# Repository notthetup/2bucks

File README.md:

# 2bucks 💰
A simple PCB with 2 DCDC (buck) regulators

## Description

This PCB solves the requirement for having 2 low-power lower voltage power rails generated from a higher voltage (usually 24V) rails for testing small project. Instead of sticking multiple small DC-DC modules which makes cabling a mess, I thought it would be simpler to make a quick PCB.

The PCB is designed to be as small as possible, and I also forgot to add any mounting holes. **Oops!**

It uses screw termnials for input and output It currently targets the [MornSun SIP DC-DC modules](https://www.mornsun-power.com/html/products/1987/regulated-output--0.5-3a.html), but it can be easily used with other 3-pin SIP DC-DC modules.

I originally created this in [EasyEDA](https://easyeda.com/) just to see how easy it is, but I am trying to moving to KiCad. I have included the EasyEDA files in the [easyeda folder](/easyeda/), and the original is [published at oshwlab](https://oshwlab.com/chinpen/2-bucks_copy)

I also played with paneling of the PCBs using [JLCPCB](https://jlcpcb.com/) to see how they come out.

## Images

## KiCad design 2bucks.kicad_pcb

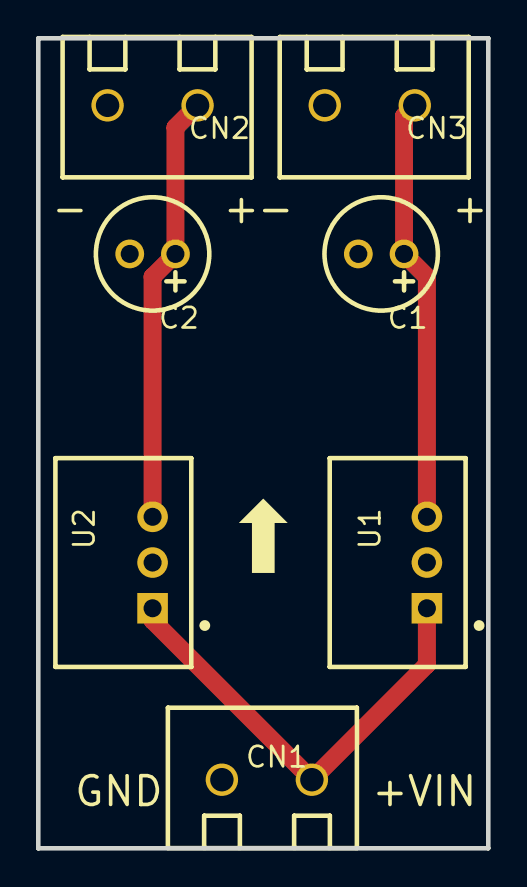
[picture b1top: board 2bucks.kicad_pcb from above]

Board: 2 copper layers, 25.0 x 45.0 mm, 7 parts (0 on the bottom side), 4 nets.

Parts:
C1, C2: 100uF; CAP-TH_BD6.3-P2.50-D1.0-FD
CN1, CN2, CN3: MX126-5.0-GN01-02P-CU-S-A; CONN-TH_2P-P5.00_MX126-5.0-GN01-02P-CU-S-A
U1: K7805-500R3; PWRM-TH_K78XX-500R3
U2: K7812-500R3; PWRM-TH_K78XX-500R3

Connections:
CN1_2: CN1.2, U1.1, U2.1
CN2_1: C2.1, CN2.1, U2.3
CN3_1: C1.1, CN3.1, U1.3
GND: C1.2, C2.2, CN1.1, CN2.2, CN3.2, U1.2, U2.2
